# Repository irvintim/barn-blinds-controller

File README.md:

# barn-blinds-controller (Vesprio VSP-WSC-4)

4-channel motorized window-shade controller: ESP32-S3-WROOM-1-N4, two TB6612FNG
H-bridges, isolated logic and motor domains, 8 wall-switch inputs. Runs ESPHome
(the owner's barn units) or Tasmota (product track).

**Rev 1.3 is the production board** (`release/v1.3`, tag `v1.3-fab`).
`main` carries Rev 1.4 development.

```
pcb/main-board/      KiCad project; lib/ (project symbols, footprints, 3D models); fab/<rev>/ (files each order was built from)
enclosure/           3D-printed case: rev2/ (current, Rev 1.2 board), archive/rev1/, reference/ (board STEP, DIN clip)
firmware/esphome/    barn-overhead, barn-windows, bench bring-up, standalone; legacy/ = Rev 1.2 pins
firmware/tasmota/    template + setup command sequence
docs/architecture.md current state: power, GPIO/terminal map, firmware rules
docs/decisions/      ADRs (why things are the way they are)
docs/bringup/        Rev 1.3 bring-up status log and procedure
docs/todo.md         TODO lists, including the Rev 1.4 change list
docs/datasheets/     part datasheets
purchasing/          JLCPCB parts inventory
```

Start with `docs/architecture.md`, then `docs/bringup/vsp-wsc4-rev13-bringup-status.md`.

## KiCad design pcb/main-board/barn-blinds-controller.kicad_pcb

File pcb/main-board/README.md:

# VSP-WSC-4 main board (KiCad 10)

Open `barn-blinds-controller.kicad_pro`. Everything the project needs is under
this folder: `lib/New_Library.kicad_sym` (U1, J4, TMP235),
`lib/barn_shade_controller.pretty/`, and `lib/3dmodels/` (referenced as
`${KIPRJMOD}/lib/3dmodels/...`). Standard KiCad libraries plus the Espressif
and JLCPCB PCM add-ons supply the rest.

- `fab/vsp-wsc4-rev1.2/`, `fab/vsp-wsc4-rev1.3/`: the files each order was
  built from. Rev 1.3 order notes: `fab/vsp-wsc4-rev1.3/JLCPCB-ORDER-NOTES.md`.
- `jlcpcb-export-steps.md`: how to generate and archive a fab set.
- `barn-blinds-controller.kicad_dru`: isolation-barrier audit rule, warning
  severity (ADR-004).
- `lib/artwork/`: silkscreen graphics sources.

Checks (from WSL, run in this folder):

```bash
K="/mnt/c/Program Files/KiCad/10.0/bin/kicad-cli.exe"
"$K" sch erc --output erc.rpt --severity-error --severity-warning barn-blinds-controller.kicad_sch   # 92 violations, 5 errors, all known
"$K" pcb drc --output drc.rpt --severity-error barn-blinds-controller.kicad_pcb                      # 0 / 0
git status   # kicad-cli can rewrite files, so check after every run
```

Branches: Rev 1.3 fixes go on `release/v1.3`; Rev 1.4 work on `main` (ADR-020).
Never move a `vX.Y-fab` tag (ADR-016).

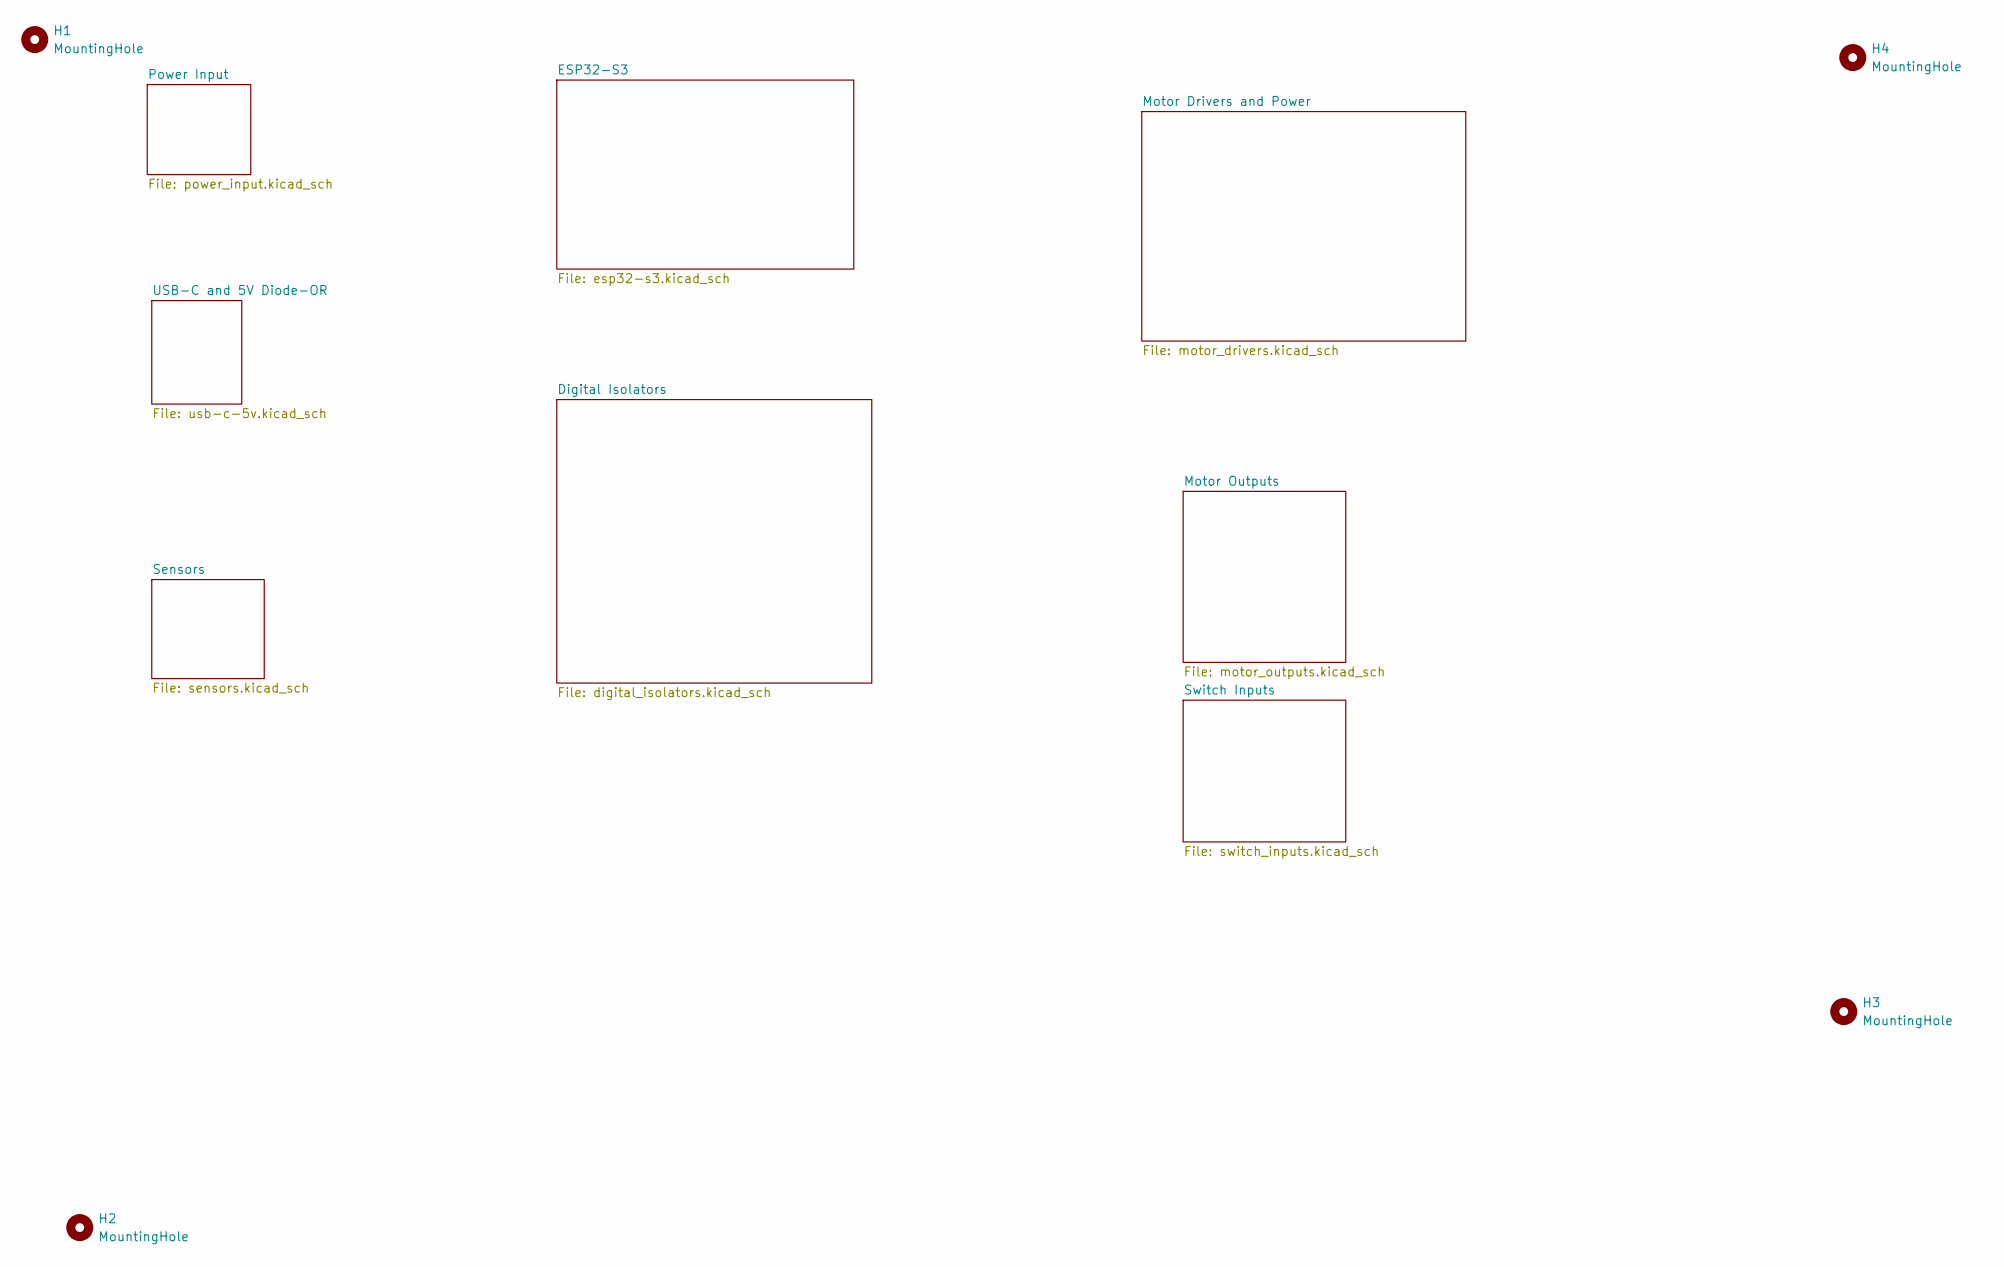
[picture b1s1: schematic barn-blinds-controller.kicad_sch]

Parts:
H1, H2, H3, H4: MountingHole; MountingHole_3.2mm_M3

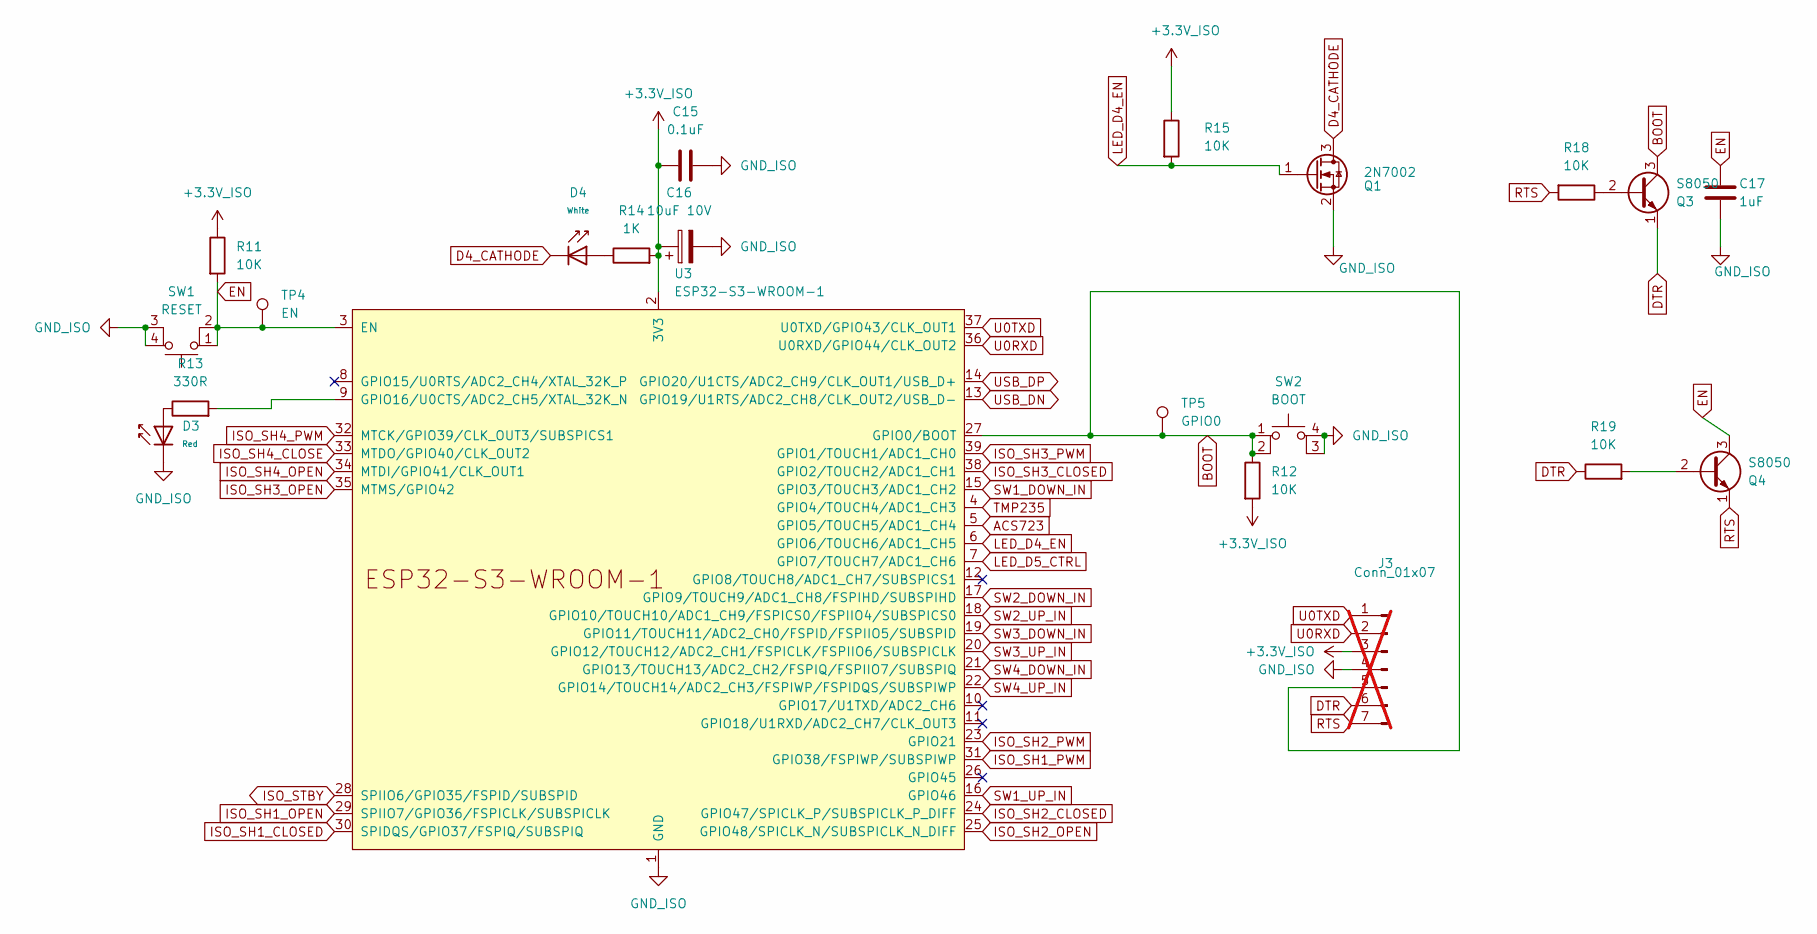
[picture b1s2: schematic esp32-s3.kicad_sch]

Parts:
C15: 0.1uF; C_0603_1608Metric; LCSC C1590
C16: 10uF 10V; C_0805_2012Metric; LCSC C17024
C17: 1uF; C_0603_1608Metric; LCSC C15849
D3: Red; D_0805_2012Metric; Forward Voltage (VF) 1.6V~2.6V; Part NCD0805R1; LCSC C84256
D4: White; D_0805_2012Metric; Forward Voltage (VF) 1.6V~2.6V; Part NCD0805R1; LCSC C84258
J3: Conn_01x07; PinHeader_1x07_P2.54mm_Vertical; LCSC C492404; not fitted
Q1: 2N7002; SOT-23; LCSC C8545
Q3, Q4: S8050; SOT-23; LCSC C2146
R11, R12, R15, R18, R19: 10K; R_0603_1608Metric; LCSC C25804
R13: 330R; R_0603_1608Metric; LCSC C23138
R14: 1K; R_0603_1608Metric; LCSC C14676
SW1: RESET; SW-SMD_4P-L3.5-W3.0-P1.50-LS4.7; LCSC C51927445
SW2: BOOT; SW-SMD_4P-L3.5-W3.0-P1.50-LS4.7; LCSC C51927445
TP4: EN; TestPoint_Pad_D1.0mm
TP5: GPIO0; TestPoint_Pad_D1.0mm
U3: ESP32-S3-WROOM-1; LCSC C2913197

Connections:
+3.3V_ISO: C15.1, C16.1, J3.3, R11.1, R12.2, R14.2, R15.1, U3.2 (3V3); also elsewhere on the board
ACS723: U3.5 (GPIO5/TOUCH5/ADC1_CH4); also elsewhere on the board
BOOT: J3.5, Q3.3 (C), R12.1, SW2.1, SW2.2, TP5.1 (1_1), U3.27 (GPIO0/BOOT)
D4_CATHODE: D4.1, Q1.3 (D)
DTR: J3.6, Q3.1 (E), R19.1
EN: C17.1, Q4.3 (C), R11.2, SW1.1, SW1.2, TP4.1 (1_1), U3.3 (EN)
GND_ISO: C15.2, C16.2, C17.2, D3.1, J3.4, Q1.2 (S), SW1.3 (K), SW1.4 (A), SW2.3 (K), SW2.4 (A), U3.1 (GND), U3.40 (GND), U3.41 (GND); also elsewhere on the board
ISO_SH1_CLOSED: U3.30 (SPIDQS/GPIO37/FSPIQ/SUBSPIQ); also elsewhere on the board
ISO_SH1_OPEN: U3.29 (SPIIO7/GPIO36/FSPICLK/SUBSPICLK); also elsewhere on the board
ISO_SH1_PWM: U3.31 (GPIO38/FSPIWP/SUBSPIWP); also elsewhere on the board
ISO_SH2_CLOSED: U3.24 (GPIO47/SPICLK_P/SUBSPICLK_P_DIFF); also elsewhere on the board
ISO_SH2_OPEN: U3.25 (GPIO48/SPICLK_N/SUBSPICLK_N_DIFF); also elsewhere on the board
ISO_SH2_PWM: U3.23 (GPIO21); also elsewhere on the board
ISO_SH3_CLOSED: U3.38 (GPIO2/TOUCH2/ADC1_CH1); also elsewhere on the board
ISO_SH3_OPEN: U3.35 (MTMS/GPIO42); also elsewhere on the board
ISO_SH3_PWM: U3.39 (GPIO1/TOUCH1/ADC1_CH0); also elsewhere on the board
ISO_SH4_CLOSE: U3.33 (MTDO/GPIO40/CLK_OUT2); also elsewhere on the board
ISO_SH4_OPEN: U3.34 (MTDI/GPIO41/CLK_OUT1); also elsewhere on the board
ISO_SH4_PWM: U3.32 (MTCK/GPIO39/CLK_OUT3/SUBSPICS1); also elsewhere on the board
ISO_STBY: U3.28 (SPIIO6/GPIO35/FSPID/SUBSPID); also elsewhere on the board
LED_D4_EN: Q1.1 (G), R15.2, U3.6 (GPIO6/TOUCH6/ADC1_CH5)
LED_D5_CTRL: U3.7 (GPIO7/TOUCH7/ADC1_CH6); also elsewhere on the board
unnamed: D3.2, R13.1
unnamed: D4.2, R14.1
unnamed: Q3.2 (B), R18.1
unnamed: Q4.2 (B), R19.2
unnamed: R13.2, U3.9 (GPIO16/U0CTS/ADC2_CH5/XTAL_32K_N)
RTS: J3.7, Q4.1 (E), R18.2
SW1_DOWN_IN: U3.15 (GPIO3/TOUCH3/ADC1_CH2); also elsewhere on the board
SW1_UP_IN: U3.16 (GPIO46); also elsewhere on the board
SW2_DOWN_IN: U3.17 (GPIO9/TOUCH9/ADC1_CH8/FSPIHD/SUBSPIHD); also elsewhere on the board
SW2_UP_IN: U3.18 (GPIO10/TOUCH10/ADC1_CH9/FSPICS0/FSPIIO4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); also elsewhere on the board
SW3_DOWN_IN: U3.19 (GPIO11/TOUCH11/ADC2_CH0/FSPID/FSPIIO5/S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); also elsewhere on the board
SW3_UP_IN: U3.20 (GPIO12/TOUCH12/ADC2_CH1/FSPICLK/FSPIIO6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); also elsewhere on the board
SW4_DOWN_IN: U3.21 (GPIO13/TOUCH13/ADC2_CH2/FSPIQ/FSPIIO7/S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); also elsewhere on the board
SW4_UP_IN: U3.22 (GPIO14/TOUCH14/ADC2_CH3/FSPIWP/FSPIDQS/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); also elsewhere on the board
TMP235: U3.4 (GPIO4/TOUCH4/ADC1_CH3); also elsewhere on the board
U0RXD: J3.2, U3.36 (U0RXD/GPIO44/CLK_OUT2)
U0TXD: J3.1, U3.37 (U0TXD/GPIO43/CLK_OUT1)
USB_DN: U3.13 (GPIO19/U1RTS/ADC2_CH8/CLK_OUT2/USB_D-); also elsewhere on the board
USB_DP: U3.14 (GPIO20/U1CTS/ADC2_CH9/CLK_OUT1/USB_D+); also elsewhere on the board

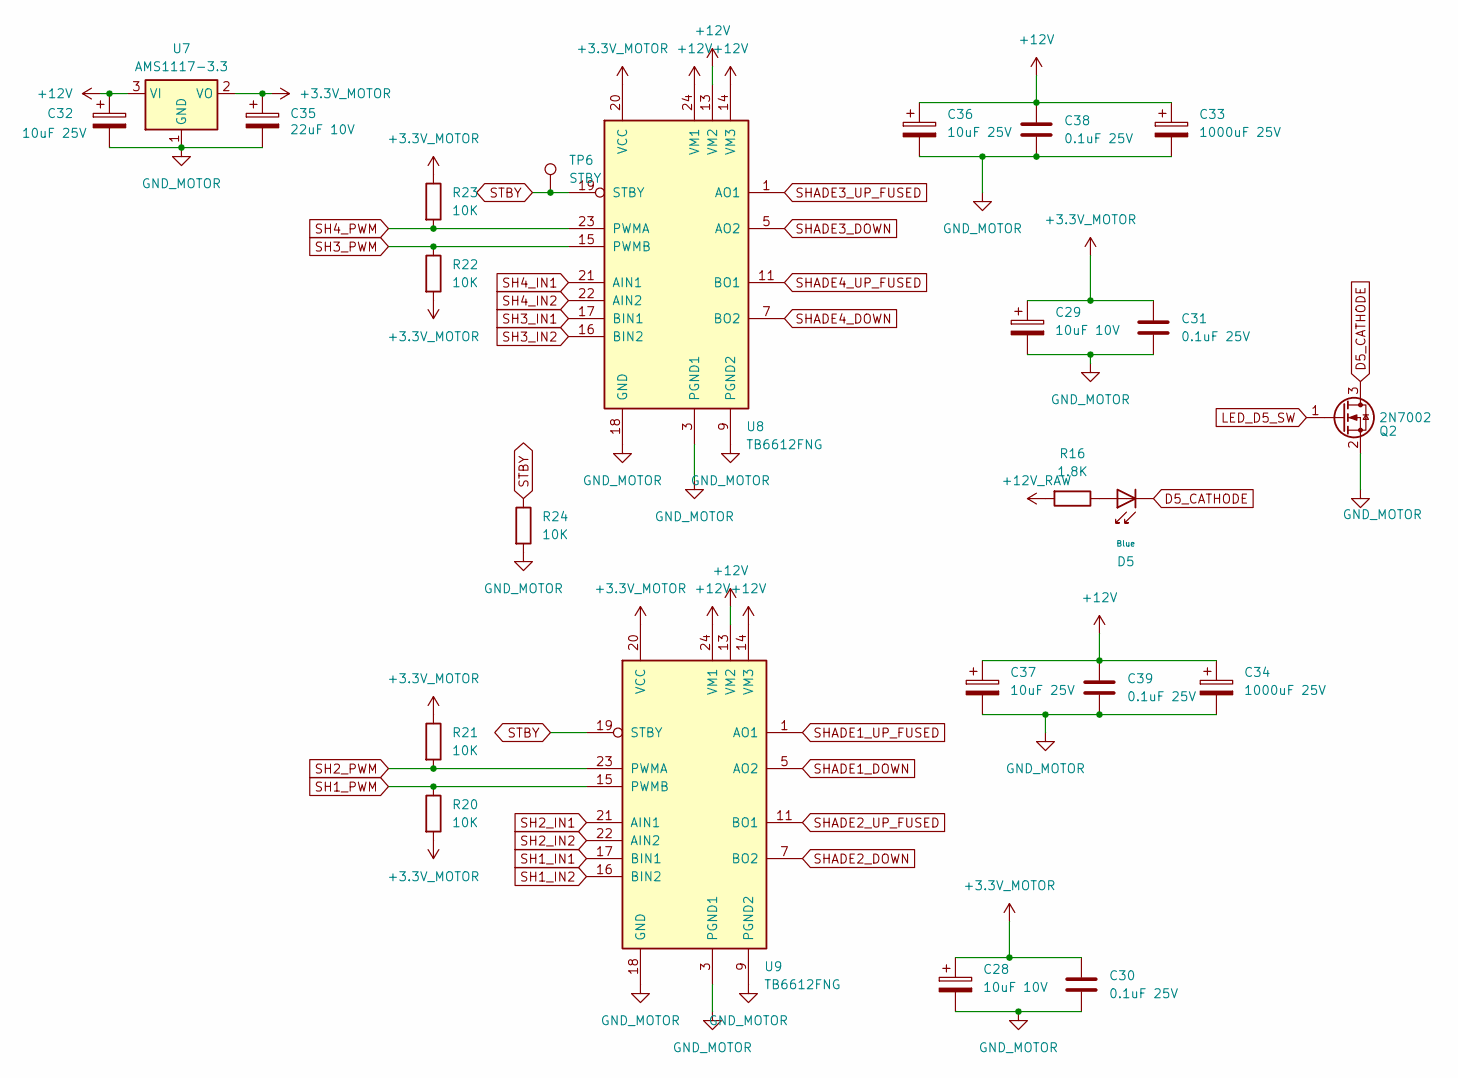
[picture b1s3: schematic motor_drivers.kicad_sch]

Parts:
C28, C29: 10uF 10V; C_0805_2012Metric; LCSC C17024
C30, C31, C38, C39: 0.1uF 25V; C_0603_1608Metric; LCSC C1590
C32, C36, C37: 10uF 25V; C_0805_2012Metric; LCSC C15850
C33, C34: 1000uF 25V; CP_Elec_10x10.5; PARTREV 10-Oct-19; LCSC C7471896
C35: 22uF 10V; C_0805_2012Metric; LCSC C29277
D5: Blue; D_0805_2012Metric; Forward Voltage (VF) 1.6V~2.6V; Part NCD0805R1; LCSC C2293
Q2: 2N7002; SOT-23; LCSC C8545
R16: 1.8K; R_0603_1608Metric; LCSC C4177
R20, R21, R22, R23, R24: 10K; R_0603_1608Metric; LCSC C25804
TP6: STBY; TestPoint_Pad_D1.0mm
U7: AMS1117-3.3; SOT-223-3_TabPin2; LCSC C6186
U8, U9: TB6612FNG; SSOP-24_5.3x8.2mm_P0.65mm; LCSC C88224

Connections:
+3.3V_MOTOR: C28.1, C29.1, C30.1, C31.1, C35.1, R20.2, R21.1, R22.2, R23.1, U7.2 (VO), U8.20 (VCC), U9.20 (VCC); also elsewhere on the board
+12V: C32.1, C33.1, C34.1, C36.1, C37.1, C38.1, C39.1, U7.3 (VI), U8.13 (VM2), U8.14 (VM3), U8.24 (VM1), U9.13 (VM2), U9.14 (VM3), U9.24 (VM1); also elsewhere on the board
+12V_RAW: R16.2; also elsewhere on the board
D5_CATHODE: D5.1, Q2.3 (D)
GND_MOTOR: C28.2, C29.2, C30.2, C31.2, C32.2, C33.2, C34.2, C35.2, C36.2, C37.2, C38.2, C39.2, Q2.2 (S), R24.2, U7.1 (GND), U8.3 (PGND1), U8.4 (PGND1), U8.9 (PGND2), U8.10 (PGND2), U8.18 (GND), U9.3 (PGND1), U9.4 (PGND1), U9.9 (PGND2), U9.10 (PGND2), U9.18 (GND); also elsewhere on the board
LED_D5_SW: Q2.1 (G); also elsewhere on the board
unnamed: D5.2, R16.1
SH1_IN1: U9.17 (BIN1); also elsewhere on the board
SH1_IN2: U9.16 (BIN2); also elsewhere on the board
SH1_PWM: R20.1, U9.15 (PWMB); also elsewhere on the board
SH2_IN1: U9.21 (AIN1); also elsewhere on the board
SH2_IN2: U9.22 (AIN2); also elsewhere on the board
SH2_PWM: R21.2, U9.23 (PWMA); also elsewhere on the board
SH3_IN1: U8.17 (BIN1); also elsewhere on the board
SH3_IN2: U8.16 (BIN2); also elsewhere on the board
SH3_PWM: R22.1, U8.15 (PWMB); also elsewhere on the board
SH4_IN1: U8.21 (AIN1); also elsewhere on the board
SH4_IN2: U8.22 (AIN2); also elsewhere on the board
SH4_PWM: R23.2, U8.23 (PWMA); also elsewhere on the board
SHADE1_DOWN: U9.5 (AO2), U9.6 (AO2); also elsewhere on the board
SHADE1_UP_FUSED: U9.1 (AO1), U9.2 (AO1); also elsewhere on the board
SHADE2_DOWN: U9.7 (BO2), U9.8 (BO2); also elsewhere on the board
SHADE2_UP_FUSED: U9.11 (BO1), U9.12 (BO1); also elsewhere on the board
SHADE3_DOWN: U8.5 (AO2), U8.6 (AO2); also elsewhere on the board
SHADE3_UP_FUSED: U8.1 (AO1), U8.2 (AO1); also elsewhere on the board
SHADE4_DOWN: U8.7 (BO2), U8.8 (BO2); also elsewhere on the board
SHADE4_UP_FUSED: U8.11 (BO1), U8.12 (BO1); also elsewhere on the board
STBY: R24.1, TP6.1 (1_1), U8.19 (STBY), U9.19 (STBY); also elsewhere on the board

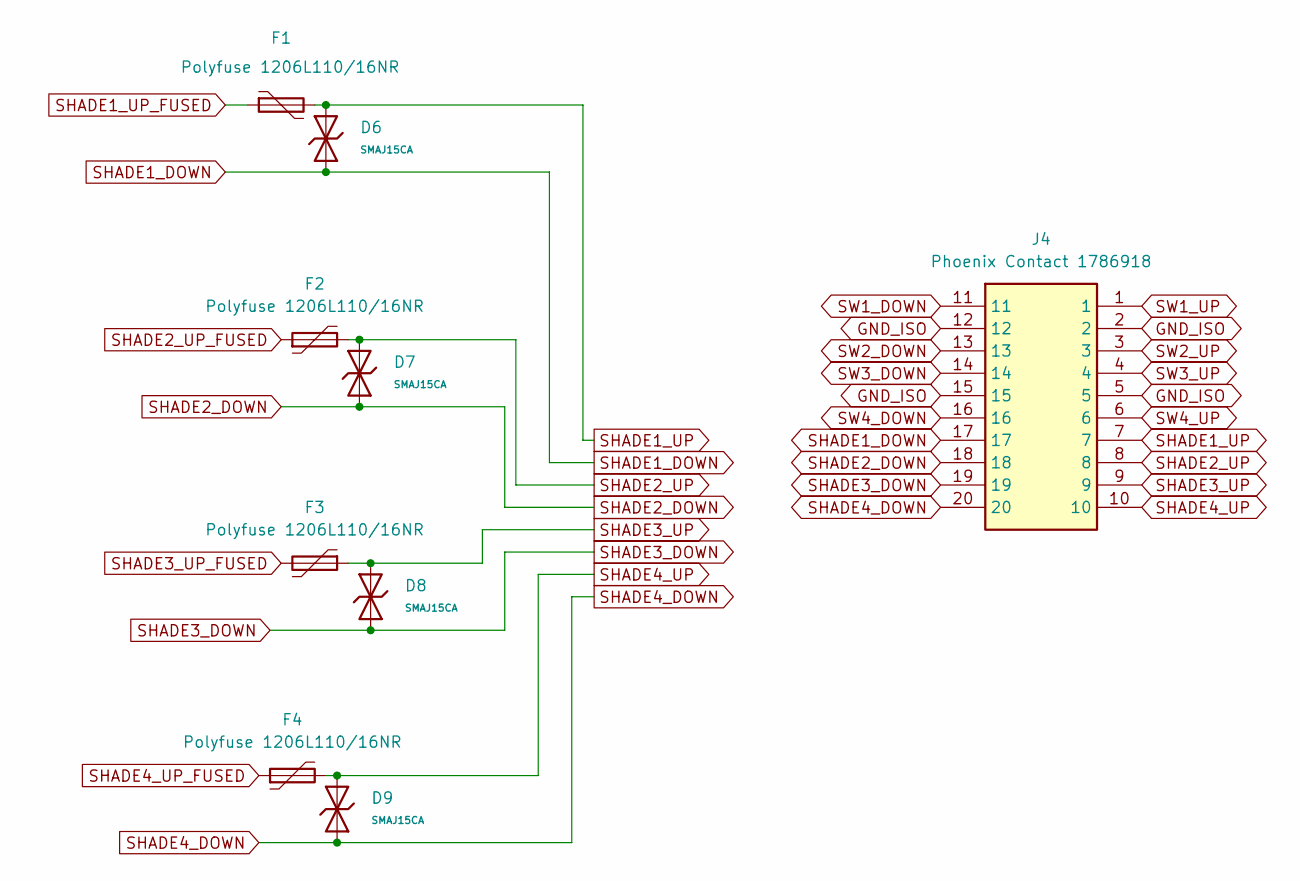
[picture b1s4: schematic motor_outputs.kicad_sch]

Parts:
D6, D7, D8, D9: SMAJ15CA; D_SMA; Clamping Voltage 19.9V; Voltage - Breakdown 13.3V; Part SMAJ15CA; LCSC C223985
F1, F2, F3, F4: Polyfuse 1206L110/16NR; Fuse_1206_3216Metric; LCSC C7542961
J4: Phoenix Contact 1786918; 1786918; Mouser Part Number 651-1786918

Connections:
GND_ISO: J4.2, J4.5, J4.12, J4.15; also elsewhere on the board
SHADE1_DOWN: D6.2, J4.17; also elsewhere on the board
SHADE1_UP: D6.1, F1.2, J4.7
SHADE1_UP_FUSED: F1.1; also elsewhere on the board
SHADE2_DOWN: D7.1, J4.18; also elsewhere on the board
SHADE2_UP: D7.2, F2.2, J4.8
SHADE2_UP_FUSED: F2.1; also elsewhere on the board
SHADE3_DOWN: D8.1, J4.19; also elsewhere on the board
SHADE3_UP: D8.2, F3.1, J4.9
SHADE3_UP_FUSED: F3.2; also elsewhere on the board
SHADE4_DOWN: D9.1, J4.20; also elsewhere on the board
SHADE4_UP: D9.2, F4.2, J4.10
SHADE4_UP_FUSED: F4.1; also elsewhere on the board
SW1_DOWN: J4.11; also elsewhere on the board
SW1_UP: J4.1; also elsewhere on the board
SW2_DOWN: J4.13; also elsewhere on the board
SW2_UP: J4.3; also elsewhere on the board
SW3_DOWN: J4.14; also elsewhere on the board
SW3_UP: J4.4; also elsewhere on the board
SW4_DOWN: J4.16; also elsewhere on the board
SW4_UP: J4.6; also elsewhere on the board

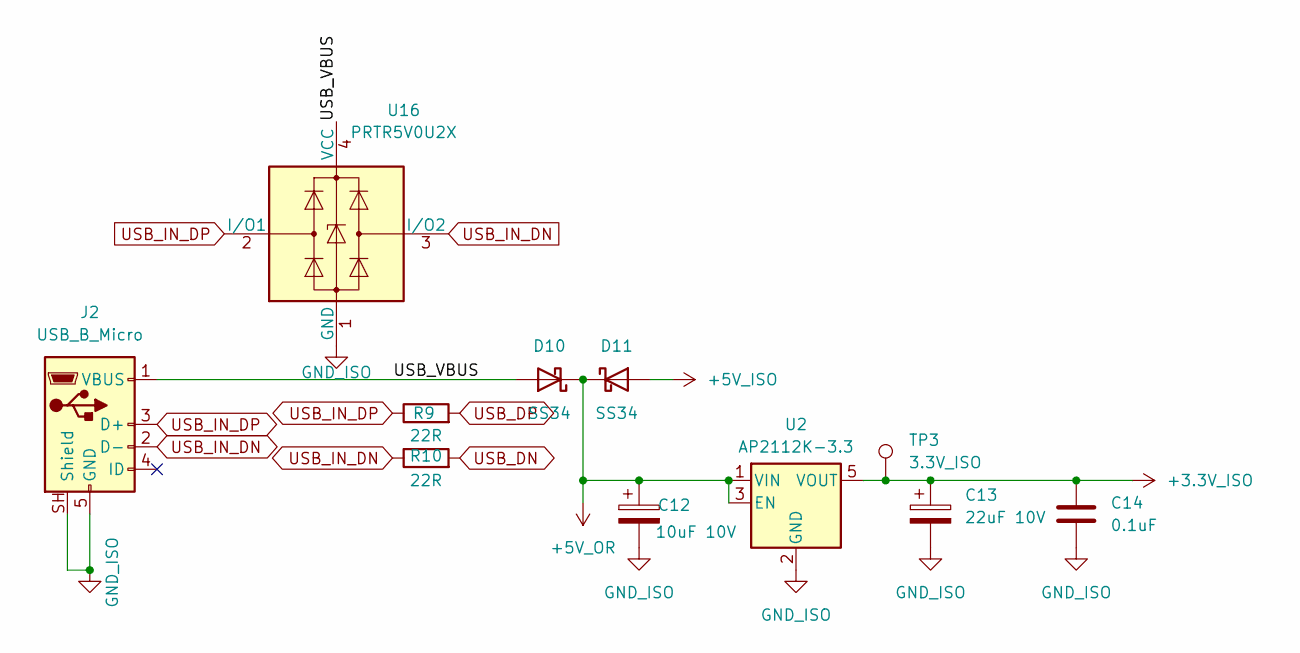
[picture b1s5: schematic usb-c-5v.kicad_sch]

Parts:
C12: 10uF 10V; C_0805_2012Metric; LCSC C17024
C13: 22uF 10V; C_0805_2012Metric; LCSC C29277
C14: 0.1uF; C_0603_1608Metric; LCSC C1590
D10, D11: SS34; D_SMA; LCSC C8678
J2: USB_B_Micro; USB_Micro-B_XKB_U254-051T-4BH83-F1S; LCSC C397452
R9, R10: 22R; R_0402_1005Metric; LCSC C25092
TP3: 3.3V_ISO; TestPoint_Pad_D1.0mm
U2: AP2112K-3.3; SOT-23-5; LCSC C23380830
U16: PRTR5V0U2X; SOT-143; LCSC C5158049

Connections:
+3.3V_ISO: C13.1, C14.1, TP3.1 (1_1), U2.5 (VOUT); also elsewhere on the board
+5V_ISO: D11.2 (A); also elsewhere on the board
+5V_OR: C12.1, D10.1 (K), D11.1 (K), U2.1 (VIN), U2.3 (EN)
/USB-C and 5V Diode-OR/USB_VBUS: D10.2 (A), J2.1 (VBUS), U16.4 (VCC)
GND_ISO: C12.2, C13.2, C14.2, J2.5 (GND), J2.SH (Shield), U2.2 (GND), U16.1 (GND); also elsewhere on the board
USB_DN: R10.2; also elsewhere on the board
USB_DP: R9.2; also elsewhere on the board
USB_IN_DN: J2.2 (D-), R10.1, U16.3 (I/O2)
USB_IN_DP: J2.3 (D+), R9.1, U16.2 (I/O1)

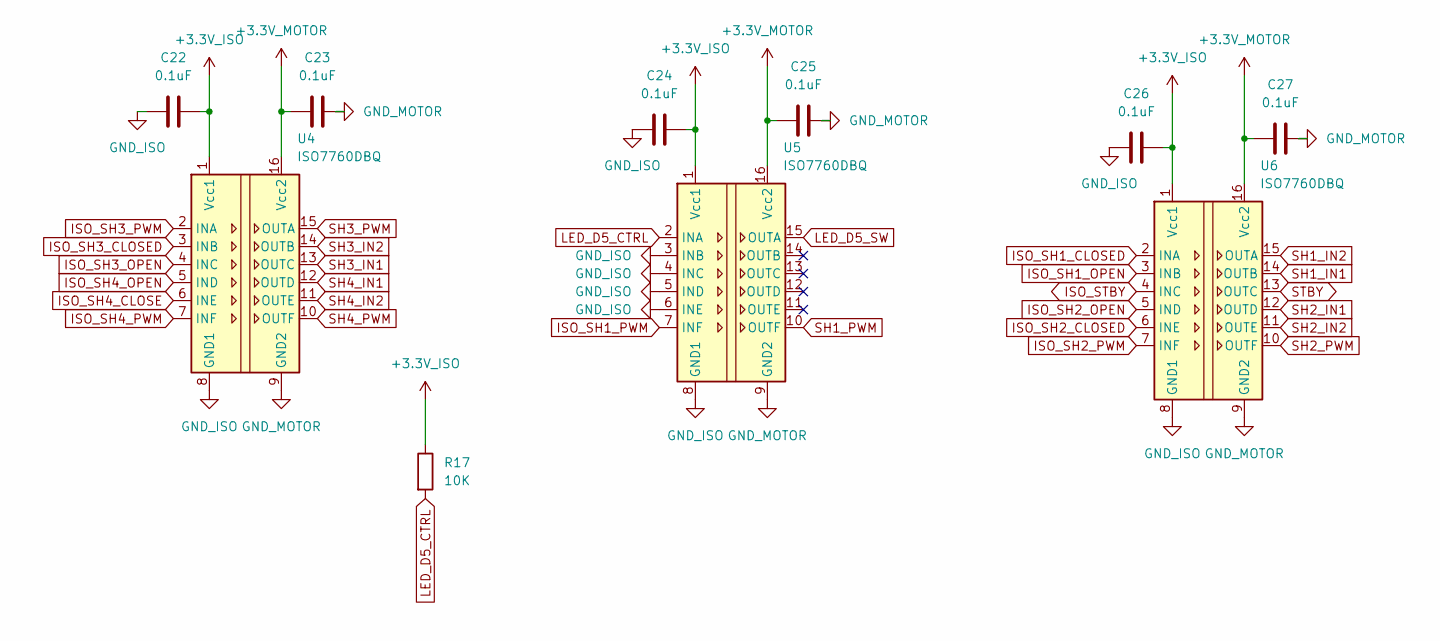
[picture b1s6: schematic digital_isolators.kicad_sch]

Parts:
C22, C23, C24, C25, C26, C27: 0.1uF; C_0603_1608Metric; LCSC C1590
R17: 10K; R_0603_1608Metric; LCSC C25804
U4, U5, U6: ISO7760DBQ; SSOP-16_3.9x4.9mm_P0.635mm; LCSC C2868628

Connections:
+3.3V_ISO: C22.2, C24.2, C26.2, R17.1, U4.1 (Vcc1), U5.1 (Vcc1), U6.1 (Vcc1); also elsewhere on the board
+3.3V_MOTOR: C23.1, C25.1, C27.1, U4.16 (Vcc2), U5.16 (Vcc2), U6.16 (Vcc2); also elsewhere on the board
GND_ISO: C22.1, C24.1, C26.1, U4.8 (GND1), U5.3 (INB), U5.4 (INC), U5.5 (IND), U5.6 (INE), U5.8 (GND1), U6.8 (GND1); also elsewhere on the board
GND_MOTOR: C23.2, C25.2, C27.2, U4.9 (GND2), U5.9 (GND2), U6.9 (GND2); also elsewhere on the board
ISO_SH1_CLOSED: U6.2 (INA); also elsewhere on the board
ISO_SH1_OPEN: U6.3 (INB); also elsewhere on the board
ISO_SH1_PWM: U5.7 (INF); also elsewhere on the board
ISO_SH2_CLOSED: U6.6 (INE); also elsewhere on the board
ISO_SH2_OPEN: U6.5 (IND); also elsewhere on the board
ISO_SH2_PWM: U6.7 (INF); also elsewhere on the board
ISO_SH3_CLOSED: U4.3 (INB); also elsewhere on the board
ISO_SH3_OPEN: U4.4 (INC); also elsewhere on the board
ISO_SH3_PWM: U4.2 (INA); also elsewhere on the board
ISO_SH4_CLOSE: U4.6 (INE); also elsewhere on the board
ISO_SH4_OPEN: U4.5 (IND); also elsewhere on the board
ISO_SH4_PWM: U4.7 (INF); also elsewhere on the board
ISO_STBY: U6.4 (INC); also elsewhere on the board
LED_D5_CTRL: R17.2, U5.2 (INA); also elsewhere on the board
LED_D5_SW: U5.15 (OUTA); also elsewhere on the board
SH1_IN1: U6.14 (OUTB); also elsewhere on the board
SH1_IN2: U6.15 (OUTA); also elsewhere on the board
SH1_PWM: U5.10 (OUTF); also elsewhere on the board
SH2_IN1: U6.12 (OUTD); also elsewhere on the board
SH2_IN2: U6.11 (OUTE); also elsewhere on the board
SH2_PWM: U6.10 (OUTF); also elsewhere on the board
SH3_IN1: U4.13 (OUTC); also elsewhere on the board
SH3_IN2: U4.14 (OUTB); also elsewhere on the board
SH3_PWM: U4.15 (OUTA); also elsewhere on the board
SH4_IN1: U4.12 (OUTD); also elsewhere on the board
SH4_IN2: U4.11 (OUTE); also elsewhere on the board
SH4_PWM: U4.10 (OUTF); also elsewhere on the board
STBY: U6.13 (OUTC); also elsewhere on the board

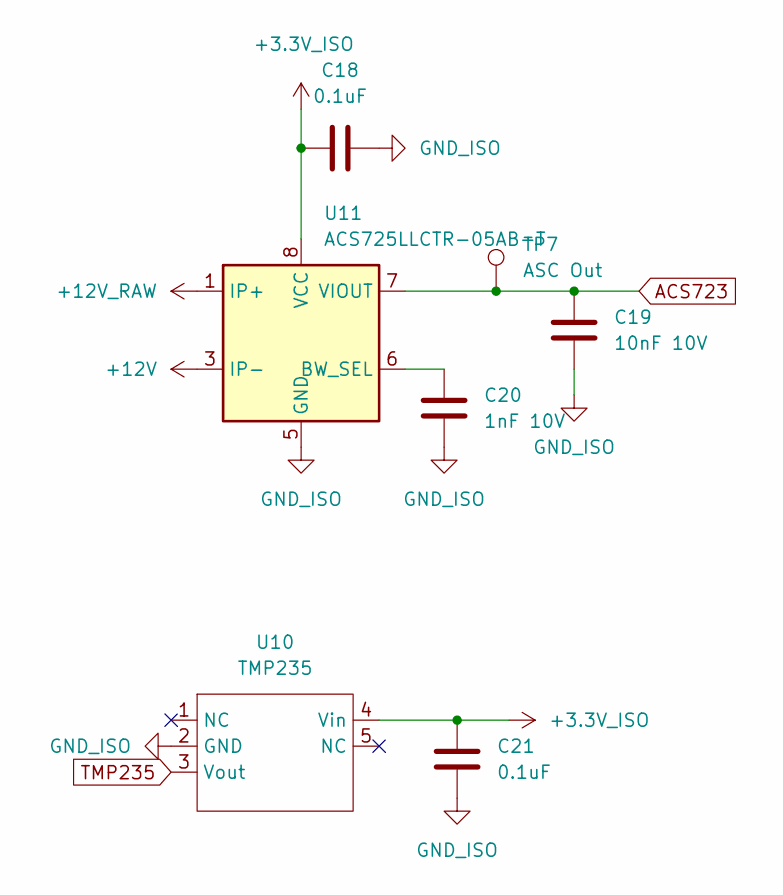
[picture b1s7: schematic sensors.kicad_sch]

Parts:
C18, C21: 0.1uF; C_0603_1608Metric; LCSC C1590
C19: 10nF 10V; C_0603_1608Metric; LCSC C519405
C20: 1nF 10V; C_0603_1608Metric; LCSC C519402
TP7: ASC Out; TestPoint_Pad_D1.0mm
U10: TMP235; SOT-353_SC-70-5; LCSC C2861437
U11: ACS725LLCTR-05AB-T; SOIC-8_3.9x4.9mm_P1.27mm; LCSC C3684552

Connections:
+3.3V_ISO: C18.1, C21.1, U10.4 (Vin), U11.8 (VCC); also elsewhere on the board
+12V: U11.3 (IP-), U11.4 (IP-); also elsewhere on the board
+12V_RAW: U11.1 (IP+), U11.2 (IP+); also elsewhere on the board
ACS723: C19.1, TP7.1 (1_1), U11.7 (VIOUT); also elsewhere on the board
GND_ISO: C18.2, C19.2, C20.2, C21.2, U10.2 (GND), U11.5 (GND); also elsewhere on the board
unnamed: C20.1, U11.6 (BW_SEL)
TMP235: U10.3 (Vout); also elsewhere on the board

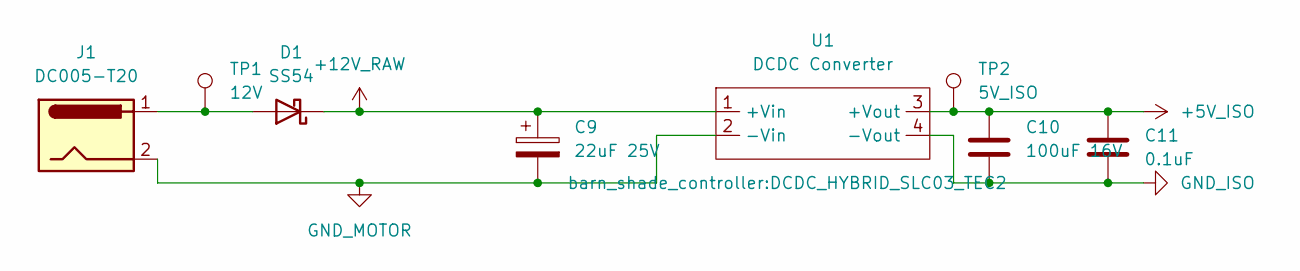
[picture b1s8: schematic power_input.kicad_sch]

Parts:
C9: 22uF 25V; C_0805_2012Metric; LCSC C45783
C10: 100uF 16V; C_1210_3225Metric; LCSC C7432790
C11: 0.1uF; C_0603_1608Metric; LCSC C1590
D1: SS54; D_SMA; LCSC C22452
J1: DC005-T20; BarrelJack_Horizontal; LCSC C111567
TP1: 12V; TestPoint_Pad_D1.0mm
TP2: 5V_ISO; TestPoint_Pad_D1.0mm
U1: DCDC Converter; DCDC_HYBRID_SLC03_TEC2; LCSC C20622657

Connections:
+5V_ISO: C10.1, C11.1, TP2.1 (1_1), U1.3 (+Vout); also elsewhere on the board
+12V_RAW: C9.1, D1.1 (K), U1.1 (+Vin); also elsewhere on the board
GND_ISO: C10.2, C11.2, U1.4 (-Vout); also elsewhere on the board
GND_MOTOR: C9.2, J1.2, U1.2 (-Vin); also elsewhere on the board
unnamed: D1.2 (A), J1.1, TP1.1 (1_1)

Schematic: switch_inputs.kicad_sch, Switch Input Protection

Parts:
C1, C2, C3, C4, C5, C6, C7, C8, C40, C41, C42, C43: 100nF; C_0402_1005Metric; LCSC C1525
R1, R2, R3, R4, R5, R6, R7, R8: 1k; R_0603_1608Metric; LCSC C14676
U12, U13, U14, U15: PRTR5V0U2X; SOT-143; LCSC C5158049

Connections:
+3.3V_ISO: C40.1, C41.1, C42.1, C43.1, U12.4 (VCC), U13.4 (VCC), U14.4 (VCC), U15.4 (VCC); also elsewhere on the board
GND_ISO: C1.2, C2.2, C3.2, C4.2, C5.2, C6.2, C7.2, C8.2, C40.2, C41.2, C42.2, C43.2, U12.1 (GND), U13.1 (GND), U14.1 (GND), U15.1 (GND); also elsewhere on the board
SW1_DOWN: R2.1; also elsewhere on the board
SW1_DOWN_IN: C2.1, R2.2, U12.2 (I/O1); also elsewhere on the board
SW1_UP: R1.1; also elsewhere on the board
SW1_UP_IN: C1.1, R1.2, U12.3 (I/O2); also elsewhere on the board
SW2_DOWN: R4.1; also elsewhere on the board
SW2_DOWN_IN: C4.1, R4.2, U13.2 (I/O1); also elsewhere on the board
SW2_UP: R3.1; also elsewhere on the board
SW2_UP_IN: C3.1, R3.2, U13.3 (I/O2); also elsewhere on the board
SW3_DOWN: R6.1; also elsewhere on the board
SW3_DOWN_IN: C6.1, R6.2, U14.2 (I/O1); also elsewhere on the board
SW3_UP: R5.1; also elsewhere on the board
SW3_UP_IN: C5.1, R5.2, U14.3 (I/O2); also elsewhere on the board
SW4_DOWN: R8.1; also elsewhere on the board
SW4_DOWN_IN: C8.1, R8.2, U15.2 (I/O1); also elsewhere on the board
SW4_UP: R7.1; also elsewhere on the board
SW4_UP_IN: C7.1, R7.2, U15.3 (I/O2); also elsewhere on the board

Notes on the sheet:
TVS VCC decoupling - one per PRTR5V0U2X (U12-U15). Place each within ~2mm of its device VCC pin (pin 4).

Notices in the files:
pcb/main-board/barn-blinds-controller.kicad_pcb:
© Vesprio.io 2026
